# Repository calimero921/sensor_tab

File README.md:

# sensor_tab
ESP32 sensor tab

External libraries : 
* BLEDevice
* BLEServer
* BLEUtils
* BLE2902
* NDEF: utility class to translate NDEF format of rfid card data (updated and corrected)
* Adafruit_NeoPixel: utility class to manage WS2812 led
* Battery Sense  for battery level 

Internal libraries : 
* cardReader: wrapper for MFRC522 library mixed with HW-178 multiplexing componenent
* readerState: data and utility class to manage reader state based on rfidData class
* rfidData: data and utility class to manage rfid card information
* pixelManager: wrapper for Adafruit Neo Pixel library to manage the set on WS2812 led, based on readerState

library

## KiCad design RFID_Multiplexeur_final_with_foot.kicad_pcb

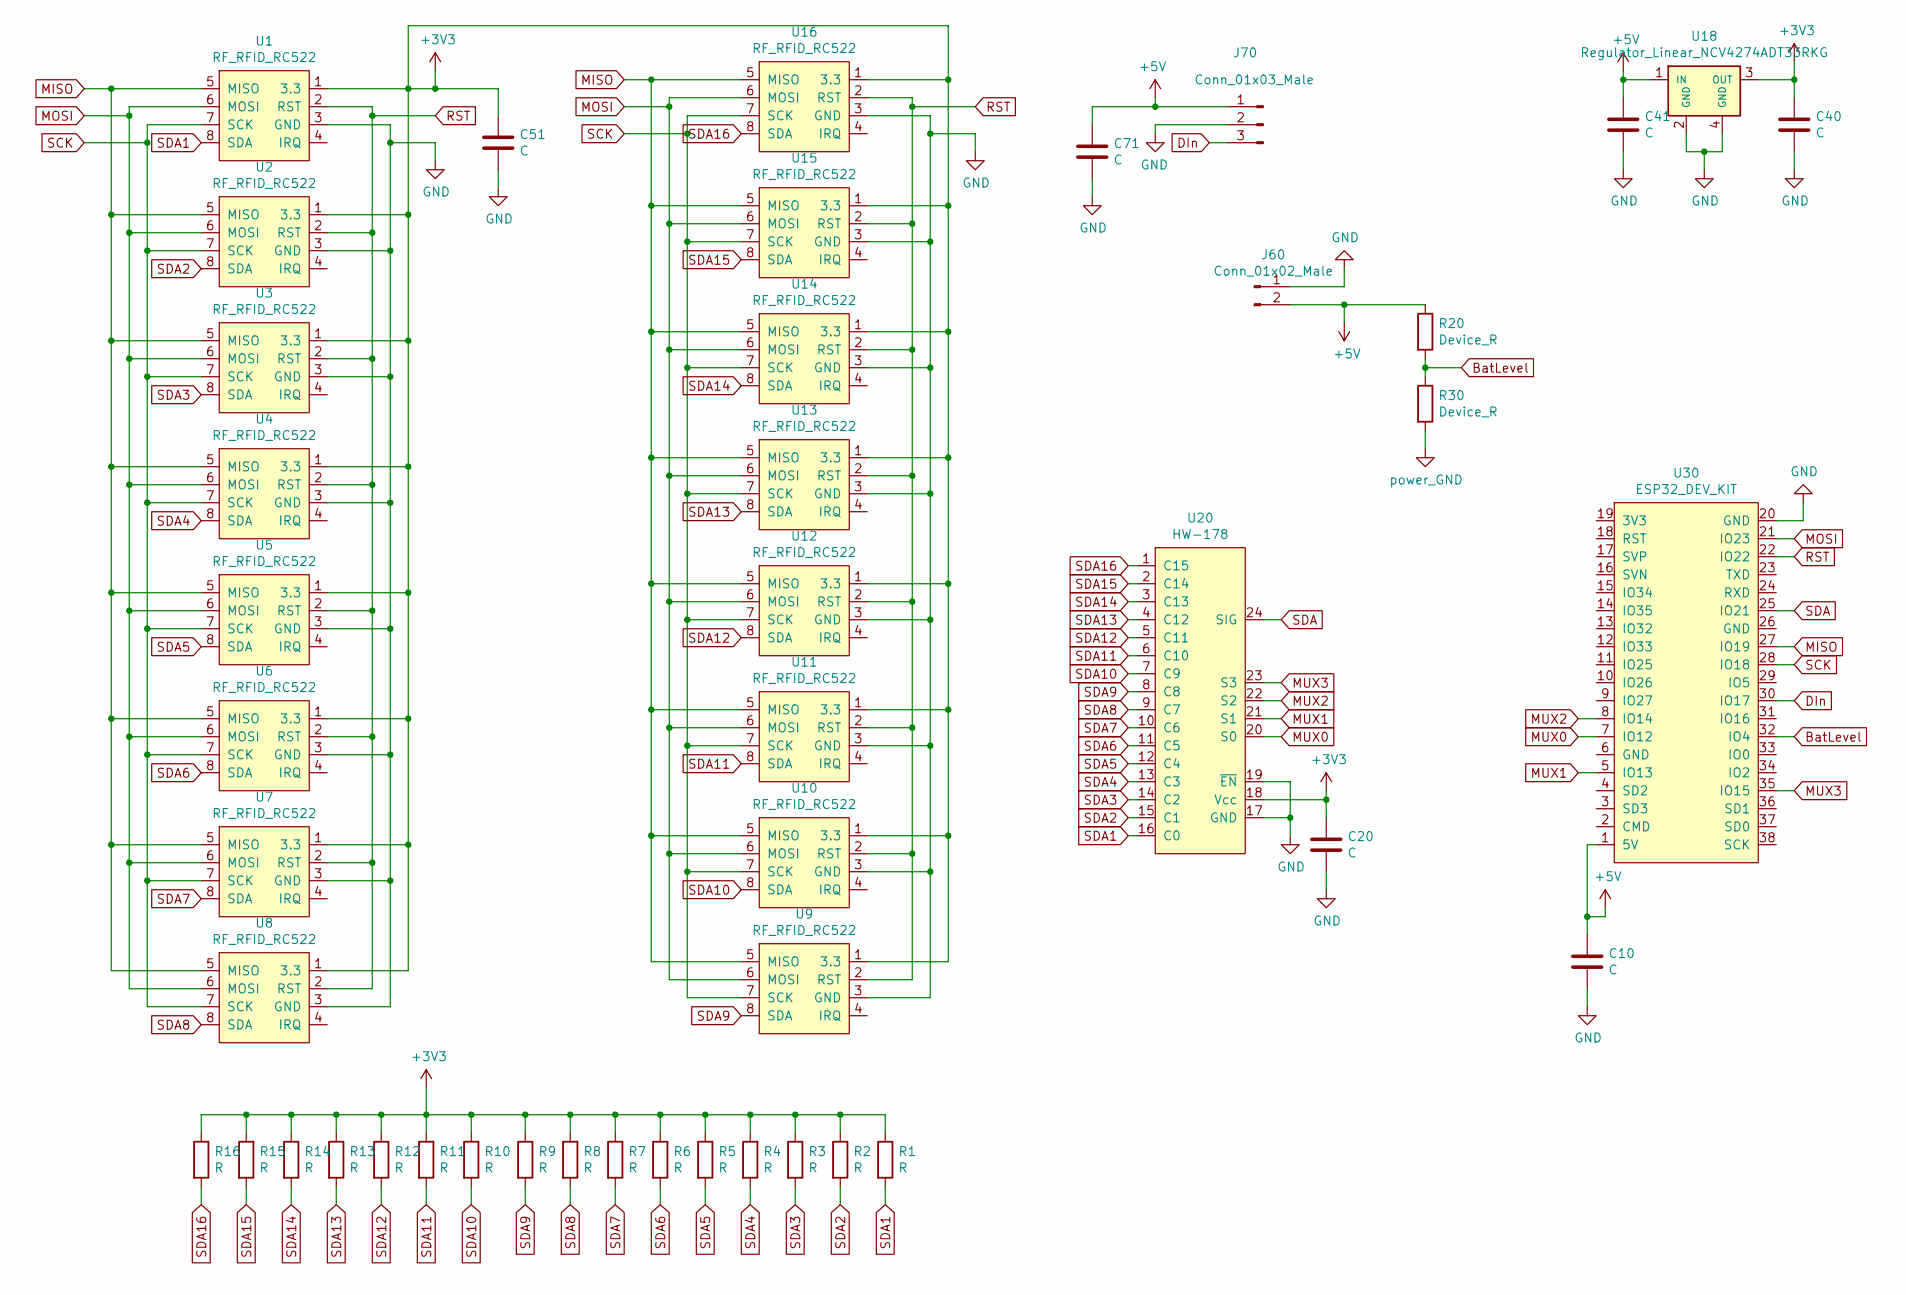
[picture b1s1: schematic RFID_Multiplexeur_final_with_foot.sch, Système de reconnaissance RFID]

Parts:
C10, C20, C71: C; CP_Radial_D10.0mm_P5.00mm
C40, C41, C51: C; CP_220uF_Eirbot
J60: Conn_01x02_Male; TerminalBlock_bornier-2_P5.08mm
J70: Conn_01x03_Male; JST_PH_S3B-PH-K_1x03_P2.00mm_Horizontal
R1, R2, R3, R4, R5, R6, R7, R8, R9, R10, R11, R12, R13, R14, R15, R16: R; R_Axial_DIN0309_L9.0mm_D3.2mm_P15.24mm_Horizontal
R20, R30: Device_R; R_Axial_DIN0309_L9.0mm_D3.2mm_P15.24mm_Horizontal
U1, U2, U3, U4, U5, U6, U7, U8, U9, U10, U11, U12, U13, U14, U15, U16: RF_RFID_RC522; JST_PH_B8B-PH-SM4-TB_1x08-1MP_P2.00mm_Vertical
U18: Regulator_Linear_NCV4274ADT33RKG; TO-252-3_TabPin4
U20: HW-178; HP4067_Demultiplexer
U30: ESP32_DEV_KIT

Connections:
+3V3: C20.1, C40.1, C51.1, R1.1, R2.1, R3.1, R4.1, R5.1, R6.1, R7.1, R8.1, R9.1, R10.1, R11.1, R12.1, R13.1, R14.1, R15.1, R16.1, U1.1 (3.3), U2.1 (3.3), U3.1 (3.3), U4.1 (3.3), U5.1 (3.3), U6.1 (3.3), U7.1 (3.3), U8.1 (3.3), U9.1 (3.3), U10.1 (3.3), U11.1 (3.3), U12.1 (3.3), U13.1 (3.3), U14.1 (3.3), U15.1 (3.3), U16.1 (3.3), U18.3 (OUT), U20.18 (Vcc); also elsewhere on the board
+5V: C10.1, C41.1, C71.1, J60.2, J70.1, R20.1, U18.1 (IN), U30.1 (5V)
BatLevel: R20.2, R30.1, U30.32 (IO4)
DIn: J70.3, U30.30 (IO17)
MISO: U1.5 (MISO), U2.5 (MISO), U3.5 (MISO), U4.5 (MISO), U5.5 (MISO), U6.5 (MISO), U7.5 (MISO), U8.5 (MISO), U9.5 (MISO), U10.5 (MISO), U11.5 (MISO), U12.5 (MISO), U13.5 (MISO), U14.5 (MISO), U15.5 (MISO), U16.5 (MISO), U30.27 (IO19); also elsewhere on the board
MOSI: U1.6 (MOSI), U2.6 (MOSI), U3.6 (MOSI), U4.6 (MOSI), U5.6 (MOSI), U6.6 (MOSI), U7.6 (MOSI), U8.6 (MOSI), U9.6 (MOSI), U10.6 (MOSI), U11.6 (MOSI), U12.6 (MOSI), U13.6 (MOSI), U14.6 (MOSI), U15.6 (MOSI), U16.6 (MOSI), U30.21 (IO23); also elsewhere on the board
MUX0: U20.20 (S0), U30.7 (IO12)
MUX1: U20.21 (S1), U30.5 (IO13)
MUX2: U20.22 (S2), U30.8 (IO14)
MUX3: U20.23 (S3), U30.35 (IO15)
RST: U1.2 (RST), U2.2 (RST), U3.2 (RST), U4.2 (RST), U5.2 (RST), U6.2 (RST), U7.2 (RST), U8.2 (RST), U9.2 (RST), U10.2 (RST), U11.2 (RST), U12.2 (RST), U13.2 (RST), U14.2 (RST), U15.2 (RST), U16.2 (RST), U30.22 (IO22); also elsewhere on the board
SCK: U1.7 (SCK), U2.7 (SCK), U3.7 (SCK), U4.7 (SCK), U5.7 (SCK), U6.7 (SCK), U7.7 (SCK), U8.7 (SCK), U9.7 (SCK), U10.7 (SCK), U11.7 (SCK), U12.7 (SCK), U13.7 (SCK), U14.7 (SCK), U15.7 (SCK), U16.7 (SCK), U30.28 (IO18); also elsewhere on the board
SDA: U20.24 (SIG), U30.25 (IO21)
SDA1: R1.2, U1.8 (SDA), U20.16 (C0)
SDA2: R2.2, U2.8 (SDA), U20.15 (C1)
SDA3: R3.2, U3.8 (SDA), U20.14 (C2)
SDA4: R4.2, U4.8 (SDA), U20.13 (C3)
SDA5: R5.2, U5.8 (SDA), U20.12 (C4)
SDA6: R6.2, U6.8 (SDA), U20.11 (C5)
SDA7: R7.2, U7.8 (SDA), U20.10 (C6)
SDA8: R8.2, U8.8 (SDA), U20.9 (C7); also elsewhere on the board
SDA9: R9.2, U9.8 (SDA), U20.8 (C8)
SDA10: R10.2, U10.8 (SDA), U20.7 (C9)
SDA11: R11.2, U11.8 (SDA), U20.6 (C10); also elsewhere on the board
SDA12: R12.2, U12.8 (SDA), U20.5 (C11)
SDA13: R13.2, U13.8 (SDA), U20.4 (C12)
SDA14: R14.2, U14.8 (SDA), U20.3 (C13)
SDA15: R15.2, U15.8 (SDA), U20.2 (C14)
SDA16: R16.2, U16.8 (SDA), U20.1 (C15)

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
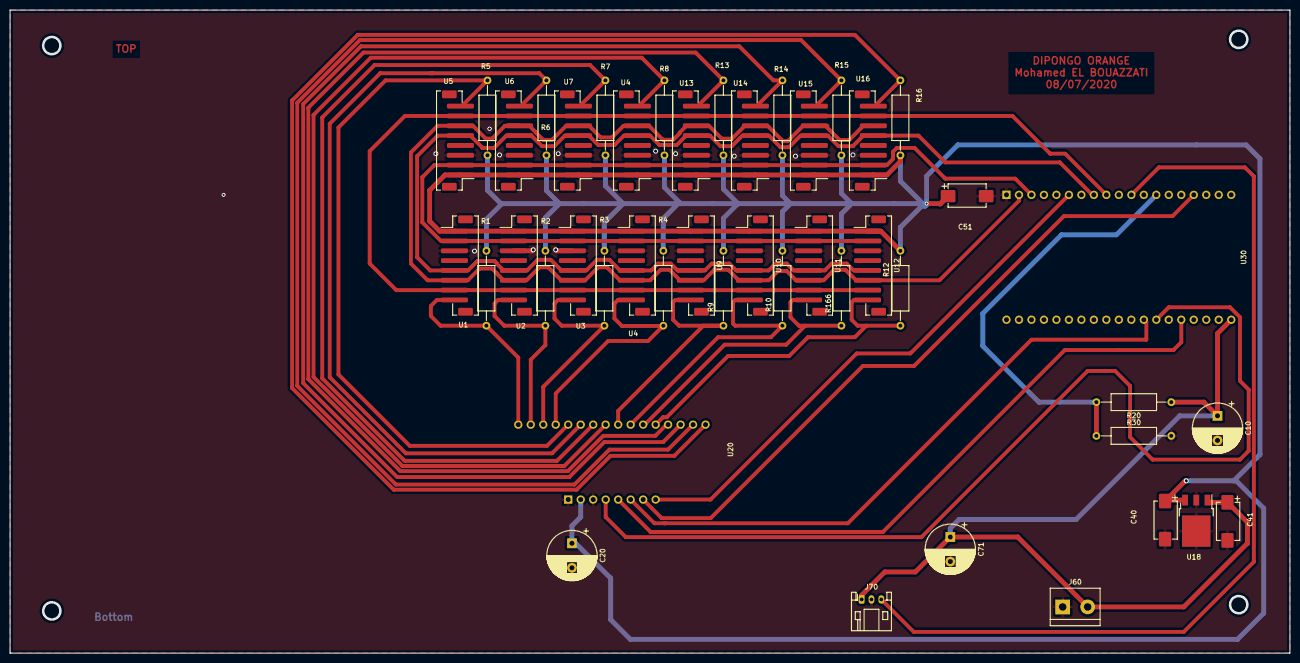
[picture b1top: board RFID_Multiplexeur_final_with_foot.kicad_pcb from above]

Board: 2 copper layers, 260.4 x 130.8 mm, 45 parts (0 on the bottom side), 30 nets.

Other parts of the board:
R166: R; R_Axial_DIN0309_L9.0mm_D3.2mm_P15.24mm_Horizontal
U4#2: RF_RFID_RC522; JST_PH_B8B-PH-SM4-TB_1x08-1MP_P2.00mm_Vertical

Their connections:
+3V3: R166.1, U4#2.1; also elsewhere on the board
MISO: U4#2.5; also elsewhere on the board
MOSI: U4#2.6; also elsewhere on the board
RST: U4#2.2; also elsewhere on the board
SCK: U4#2.7; also elsewhere on the board
SDA8: U4#2.8; also elsewhere on the board
SDA11: R166.2; also elsewhere on the board

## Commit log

2019-05-13 [FEATURE] Test commit fred
2019-05-14 Update main.cpp
    Add WS2812 driver
    Add MFRC522 driver
2019-07-03 Ajout lecture tag Mifare
    Ajout lecture tag Mifare
2019-07-03 Mise à jour lecture de tag et interprétation couleur
2019-07-11 Prise en charge multiplexeur
2019-09-06 Refactor du coeur en bibliothèques
2019-09-13 Migration vers VSCode
2019-09-13 Mise à jour .gitignore préparation commentaire en tête de fichier
2019-09-13 Mise à jour affichage des logs de debug
2019-09-16 Refactor cardreadeur
2020-02-10 refactor
2020-02-12 update PlatformIO.ini (upload speed)
2020-03-19 Update for prototype
2020-03-20 fisrt commit
2020-08-27 version final du projet
2020-08-27 Create carte electronique
2020-08-28 16 antennes avec niveau de batterie
2020-08-28 final project
